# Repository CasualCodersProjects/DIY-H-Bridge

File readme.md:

# Casual Coders DIY H-Bridge Kit
The H-Bridge is a simple circuit which enables the user to switch the polarity of a voltage across it's output terminals. This is often necessary to allow bidirectional control of DC motors.  

This DIY Kit includes:
- 2x Base PCBs which must be populated with 2x NMOS and 2x PMOS each. This board has built in Pull-Down reistors and PMOS Drivers.
- 2.54mm pitch header pins for logic inputs.
- 60V MAX input voltage.

This kit is designed such that the user may select their own MOSFETS specific to their application. This facilitates learning about mosfet characteristics and allows you to optimize characristics such as on resistance, gate threshold, drain-source voltage, and more. As such, this is essentially an Application Specific H Bridge.

You may instead elect to select a premade configuration by Casual Coders. Our premade configuration should be functional for most applications, but is comprablly costly. We include:
- 4x [MPG50N06](https://datasheet.lcsc.com/lcsc/2206211730_Minos-MPG50N06_C2980287.pdf) (NMOS) with an Id of 50A, on Resistance of 12.5mΩ, and Vds of 60V.
- 4x [IFR9Z34NPBF](https://www.infineon.com/dgdl/irf9z34npbf.pdf?fileId=5546d462533600a40153561220af1ddd) (PMOS) with an Id of -19A, on Resistance of 100mΩ, and Vds of -55V.
- 4x Screw Terminals.  

Diagram:

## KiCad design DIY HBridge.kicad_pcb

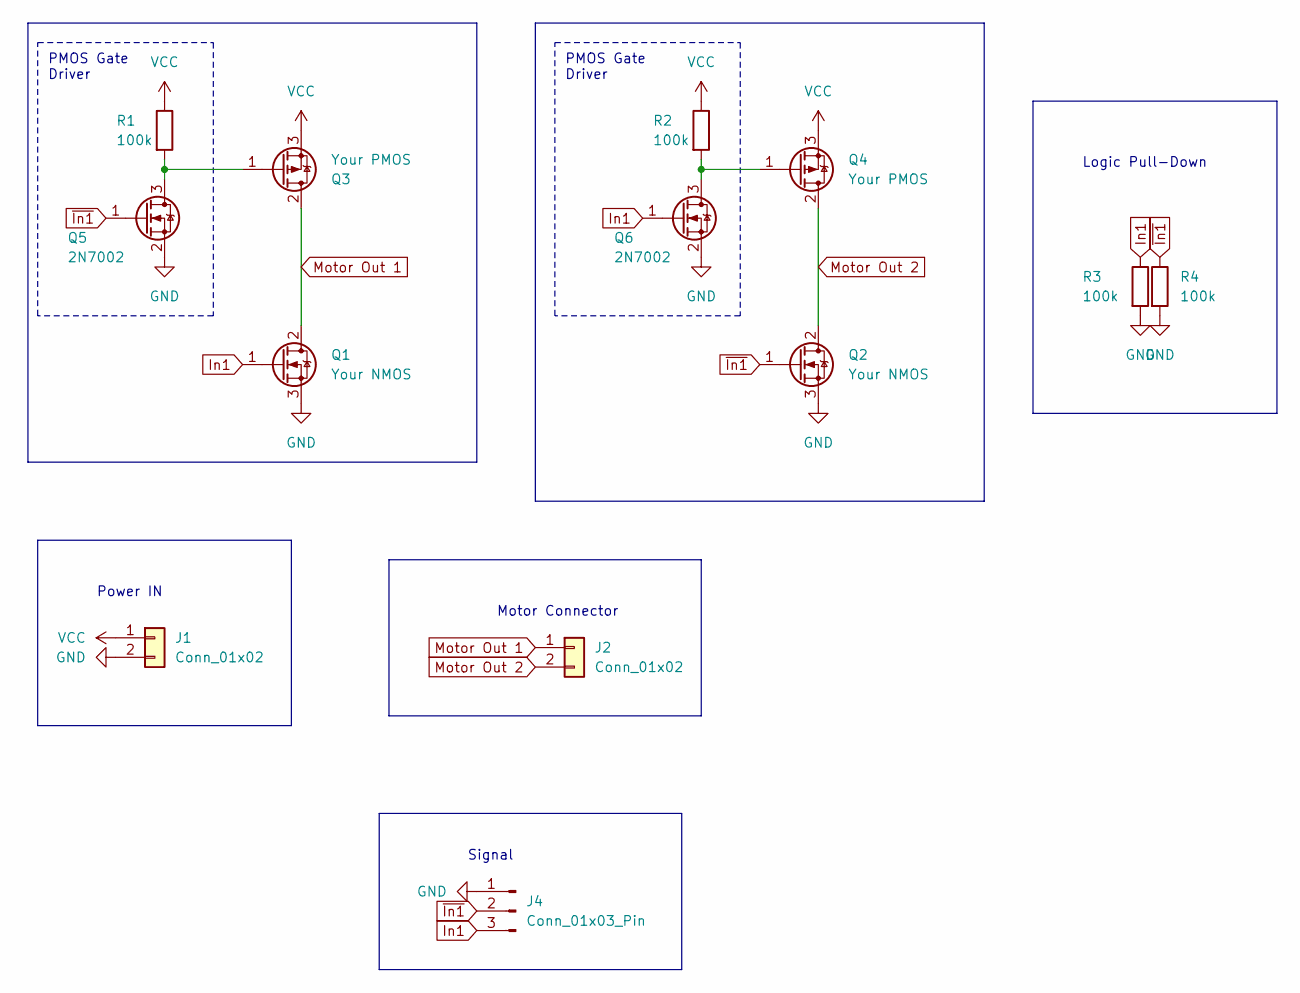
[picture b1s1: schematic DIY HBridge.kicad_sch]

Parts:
J1, J2: Conn_01x02; TerminalBlock_Phoenix_MKDS-1,5-2-5.08_1x02_P5.08mm_Horizont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
J4: Conn_01x03_Pin; PinHeader_1x03_P2.54mm_Vertical
Q1, Q2: Your NMOS; TO-220-3_Vertical
Q3, Q4: Your PMOS; TO-220-3_Vertical
Q5, Q6: 2N7002; SOT-23
R1, R2, R3, R4: 100k; R_0603_1608Metric

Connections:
GND: J1.2, J4.1, Q1.3 (S), Q2.3 (S), Q5.2 (S), Q6.2 (S), R3.2, R4.2
In1: J4.3, Q1.1 (G), Q6.1 (G), R3.1
Motor Out 1: J2.1, Q1.2 (D), Q3.2 (D)
Motor Out 2: J2.2, Q2.2 (D), Q4.2 (D)
unnamed: Q3.1 (G), Q5.3 (D), R1.2
unnamed: Q4.1 (G), Q6.3 (D), R2.2
VCC: J1.1, Q3.3 (S), Q4.3 (S), R1.1, R2.1
~In1: J4.2, Q2.1 (G), Q5.1 (G), R4.1

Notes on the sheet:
PMOS Gate Driver
Motor Connector
Power IN
Signal
Logic Pull-Down

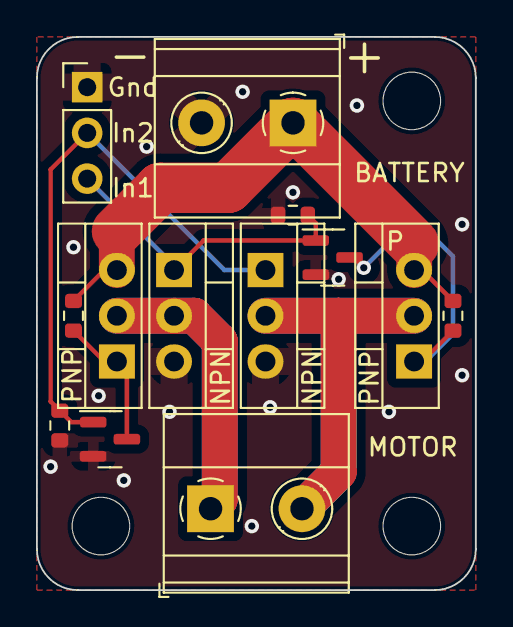
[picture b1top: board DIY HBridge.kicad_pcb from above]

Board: 2 copper layers, 24.4 x 30.7 mm, 13 parts (0 on the bottom side), 8 nets.

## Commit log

2023-12-30 fixc images
2023-12-30 fix readme
